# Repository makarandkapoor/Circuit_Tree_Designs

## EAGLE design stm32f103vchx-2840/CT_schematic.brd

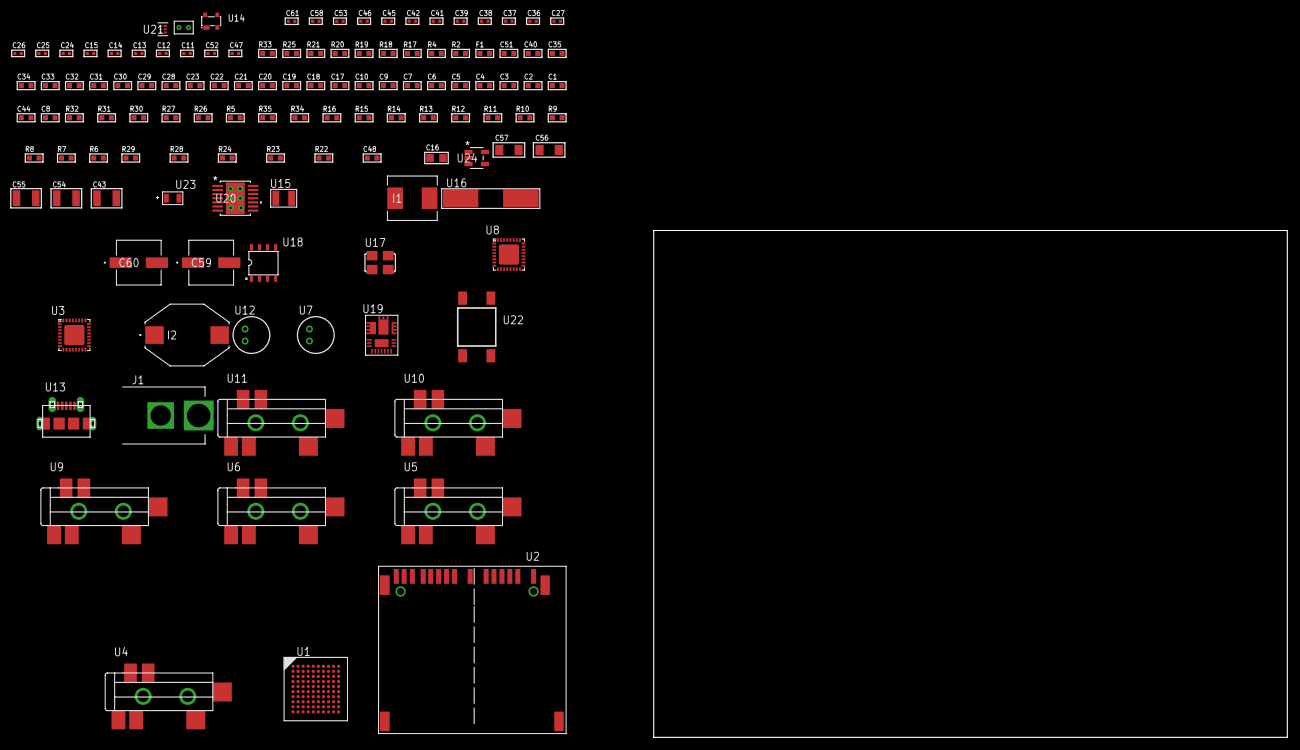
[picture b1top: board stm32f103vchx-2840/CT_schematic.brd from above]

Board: 2 copper layers, 121 parts (0 on the bottom side), 82 nets, no tracks yet.

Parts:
C1, C10, C17, C18, C19, C20, C21, C22, C23, C28, C29, C30, C31, C32, C33, C34, C35, C40, C51: 1e-06; C0603
C2, C3, C4, C5, C6, C7: 1e-07; C0603
C8: 4.7e-06; C0603
C9: 1e-08; C0603
C11, C12, C13, C14: 1e-11; C0402
C15, C24, C25, C26, C27, C36, C37, C38, C39, C45, C46, C53, C58: 1e-07; C0402
C16: 1e-05; C0805
C41, C42, C61: 1e-08; C0402
C43: 0.0001; C1210
C44: 2.2e-06; C0603
C47: 8.2e-09; C0402
C48: 2.724074888439e-07; R0603
C52: 3.3e-09; C0402
C54, C55: 2.2e-05; C1210
C56, C57: 1e-05; C1206
C59, C60: 0.0001; EXV-9H
F1: 240.0; L0603
I1: 6.8e-07; IND25X25CZ
I2: 1e-05; IND_PM3316
J1: PJ-037B; PJ-037B_PACKAGE
R2: 1000.0; R0603
R4: 4700.0; R0603
R5, R31, R32: 10000.0; R0603
R6, R7, R8, R9, R10, R11, R12, R13, R14, R15, R16: 100000.0; R0603
R17, R18, R19, R20: 1270.0; R0603
R21: 0.1; R0603
R22: 4030.2416170974; R0603
R23: 2878.7440122125; R0603
R24: 63.795609756098; R0603
R25: 130.0; R0603
R26: 39000.0; R0603
R27: 49900.0; R0603
R28: 5286.7027027027; R0603
R29: 71007.101651032; R0603
R30: 22000.0; R0603
R33: 9100.0; R0603
R34: 680000.0; R0603
R35: 120000.0; R0603
U1: stm32f103vch6; LFBGA100
U2: 10100565
U3, U8: SGTL5000XNAA3; QFN-32
U4, U5, U6, U9, U10, U11: SJ-43515TS-SMT-TR
U7, U12: WM-64PCT; WM-64PC
U13: 47590-0001; MICRO_USB_AB
U14: prtr5v0u2ax; SOT143B
U15: ABS07-32.768KHZ-7-T
U16: ABLS-25.000MHZ-B2F-T
U17: ASFL-24.57MHZ-NCS; ASFL1
U18: idt74fct38072; IDT74FCT38072
U19: IR3899MTR1PBF
U20: tps54225PWP; HTSSOP14
U21: TPS3895ADRYR; SON-6
U22: 4-1437565-2; SW_4-1437565-2
U23: Q65110A2395; LGM67K-G1J2-24-Z
U24: nc7sz125m5x; NC7SZ125M5X
U25: Dummy; DUMMY_PACKAGE_235

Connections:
CLK_CRYSTAL_U1_A1: C11.1, U1.A1, U15.1
CLK_CRYSTAL_U1_B1: C12.1, U1.B1, U15.2
CLK_CRYSTAL_U1_C1: C13.1, U1.C1, U16.1
CLK_CRYSTAL_U1_D1: C14.1, U1.D1, U16.2
CLK_U3_21: U3.21, U18.7
CLK_U8_21: U8.21, U18.6
CLK_U18_3: U17.3, U18.3
GND: C1.2, C2.2, C3.2, C4.2, C5.2, C6.2, C7.2, C8.2, C9.2, C10.2, C11.2, C12.2, C13.2, C14.2, C15.2, C16.2, C24.2, C25.2, C26.2, C27.2, C28.2, C36.2, C37.2, C38.2, C39.2, C40.2, C41.2, C42.2, C44.2, C45.2, C46.2, C51.2, C52.2, C54.2, C55.2, C56.2, C57.2, C58.2, C59.2, C60.2, C61.2, J1.2, R2.2, R5.2, R18.2, R20.2, R21.1, R21.2, R23.2, R26.2, R28.2, R30.2, R33.2, R35.2, U1.C2, U1.E4, U1.E5, U1.E6, U1.E7, U1.G1, U1.H1, U2.6, U2.10, U2.12, U2.16, U2.17, U2.20, U2.21, U3.1, U3.3, U3.7, U3.EXP, U5.1, U6.1, U7.2, U8.1, U8.3, U8.7, U8.EXP, U10.1, U11.1, U12.2, U13.5, U13.6, U13.7, U13.8, U13.9, U14.1, U17.2, U18.4, U18.5, U18.8, U19.4, U19.11, U19.17, U20.5, U20.8, U20.9, U20.15, U21.2, U23.C, U24.1, U24.3, U25.1
NET_U1_D5: R5.1, U1.D5
NET_U1_E1: R4.1, U1.E1, U24.4
NET_U1_K1: C9.1, C10.1, F1.1, U1.J1, U1.K1
NET_U1_K10: U22.3, U22.4
NET_U2_1: R8.1, U2.1
NET_U2_2: R7.1, U2.2
NET_U2_18: U2.18, U2.19
NET_U3_10: C27.1, U3.10
NET_U3_29: R17.1, U3.29
NET_U3_31: R18.1, U3.31
NET_U4_1: U3.4, U4.1
NET_U4_2: U3.2, U4.2
NET_U4_5: U3.6, U4.5
NET_U5_2: C18.1, U5.2
NET_U5_5: C17.1, U5.5
NET_U6_2: C20.1, C21.1, U6.2
NET_U6_5: C19.1, U6.5
NET_U6_13: C20.2, C21.2
NET_U7_1: C22.1, C23.1, C28.1, U3.16, U7.1
NET_U7_15: C22.2, C23.2
NET_U8_10: C39.1, U8.10
NET_U8_29: R19.1, U8.29
NET_U8_31: R20.1, U8.31
NET_U9_1: U8.4, U9.1
NET_U9_2: U8.2, U9.2
NET_U9_5: U8.6, U9.5
NET_U10_2: C30.1, U10.2
NET_U10_5: C29.1, U10.5
NET_U11_2: C32.1, C33.1, U11.2
NET_U11_5: C31.1, U11.5
NET_U11_13: C32.2, C33.2
NET_U12_1: C34.1, C35.1, C40.1, U8.16, U12.1
NET_U12_15: C34.2, C35.2
NET_U14_4: U13.1, U14.4
NET_U19_1: C47.1, R22.1, R23.1, R24.1, R25.1, U19.1, U19.8
NET_U19_2: C46.1, U19.2
NET_U19_3: C47.2, C48.1, C48.2, U19.3
NET_U19_5: R26.1, U19.5
NET_U19_10: C44.1, U19.10
NET_U19_12: C43.1, I1.1, U19.12
NET_U19_14: C43.2, U19.14
NET_U19_15: R27.1, R28.1, U19.15
NET_U19_ATNET_3: I1.2, R22.2
NET_U19_ATNET_4: C48.2, R24.2
NET_U20_2: R29.2, R30.1, U20.2
NET_U20_3: C51.1, U20.3
NET_U20_4: C52.1, U20.4
NET_U20_10: C53.1, I2.1, U20.10, U20.11
NET_U20_12: C53.2, U20.12
NET_U21_1: R32.1, R33.1, U21.1
NET_U21_3: R34.2, R35.1, U21.3
NET_U21_4: R31.1, U21.4, U24.2
NET_U22_1: R2.1, U22.1, U22.2
PROC_DAC_OUT2: U1.H3, U25.2
PROC_I2S2_CK: U1.J8, U3.24
PROC_I2S2_SD: U1.G8, U3.26
PROC_I2S2_WS: U1.K8, U3.23
PROC_I2S3_CK: U1.A7, U8.24
PROC_I2S3_SD: U1.C5, U8.26
PROC_I2S3_WS: U1.A8, U8.23
PROC_SDIO_CK: R6.1, U1.C8, U2.8
PROC_SDIO_D0: R9.1, U1.F9, U2.4
PROC_SDIO_D1: R10.1, U1.E9, U2.3
PROC_SDIO_D2: R11.1, U1.B9, U2.15
PROC_SDIO_D3: R12.1, U1.B8, U2.14
PROC_SDIO_D4: R13.1, U1.B4, U2.13
PROC_SDIO_D5: R14.1, U1.A4, U2.11
PROC_SDIO_D6: R15.1, U1.F10, U2.7
PROC_SDIO_D7: R16.1, U1.E10, U2.5
PROC_USB_DM: U13.2, U14.3
PROC_USB_DP: U13.3, U14.2
VCC_S1_16V4: C45.1, C56.1, C57.1, C59.1, C60.1, J1.1, R27.2, U19.9, U20.7, U20.13, U20.14
VCC_TIER1_1V2: C24.1, C36.1, I1.2, R22.2, U3.30, U8.30
VCC_TIER1_3V3: C1.1, C2.1, C3.1, C4.1, C5.1, C6.1, C7.1, C8.1, C15.1, C16.1, C25.1, C26.1, C37.1, C38.1, C41.1, C42.1, C54.1, C55.1, C58.1, C61.1, F1.2, I2.2, R4.2, R6.2, R7.2, R8.2, R9.2, R10.2, R11.2, R12.2, R13.2, R14.2, R15.2, R16.2, R17.2, R19.2, R29.1, R31.2, R32.2, R34.1, U1.B2, U1.D2, U1.F4, U1.F5, U1.F6, U1.F7, U2.9, U3.5, U3.20, U8.5, U8.20, U17.4, U18.1, U18.2, U20.1, U21.6, U24.5

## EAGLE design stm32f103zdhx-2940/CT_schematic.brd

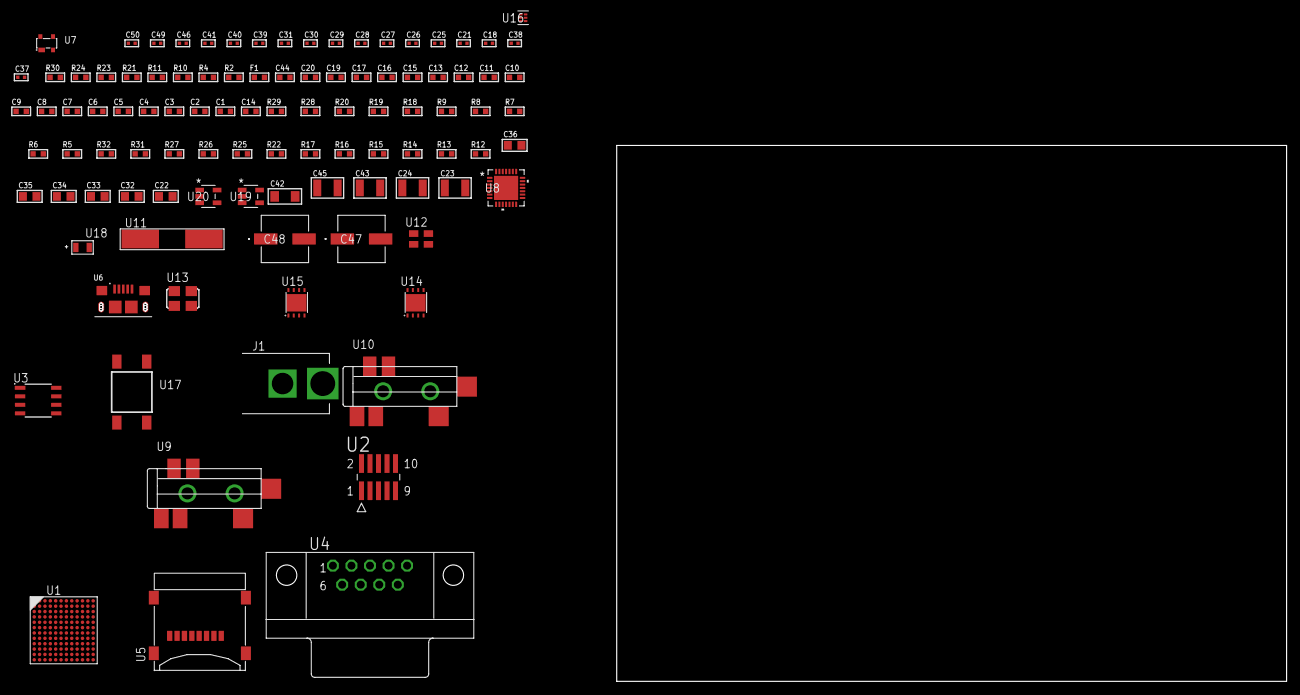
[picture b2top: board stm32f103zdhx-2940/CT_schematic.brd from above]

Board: 2 copper layers, 102 parts (0 on the bottom side), 48 nets, no tracks yet.

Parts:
C1, C17, C19, C20, C44: 1e-06; C0603
C2, C3, C4, C5, C6, C7, C8, C9, C10, C11, C12, C13: 1e-07; C0603
C14: 4.7e-06; C0603
C15, C16: 1e-08; C0603
C18, C21, C27, C28, C29, C30, C31, C46: 1e-07; C0402
C22, C32, C33, C34, C35, C36: 1e-05; C0805
C23, C24: 2.2e-05; C1210
C25, C26: 1e-09; C0402
C37, C38: 2.2e-11; C0402
C39, C40, C41, C49, C50: 1e-08; C0402
C42: 1e-05; C1206
C43, C45: 1e-05; C1210
C47, C48: 0.0001; EXV-9H
F1: 240.0; L0603
J1: PJ-037B; PJ-037B_PACKAGE
R2, R24: 1000.0; R0603
R4: 4700.0; R0603
R5, R6, R7, R8, R9, R28, R29: 10000.0; R0603
R10: 5.0; R0603
R11: 120.0; R0603
R12, R13, R14, R15, R16, R17, R22, R25, R27: 100000.0; R0603
R18, R19, R20: 47000.0; R0603
R21: 680.0; R0603
R23: 2231.0; R0603
R26: 300000.0; R0603
R30: 9100.0; R0603
R31: 680000.0; R0603
R32: 120000.0; R0603
U1: stm32f103zdh6; LFBGA144
U2: FTSH-105-01-L-DV-K; SAMTEC_FTSH-105-01-L-DV-K
U3: MCP2562-E/SN; SOIC-8
U4: 182-009-113R531; 182-009-MALE
U5: 0472192001; MOLEX_47219-2001
U6: 10118193-0001LF; FCI_10118193-0001LF
U7: prtr5v0u2ax; SOT143B
U8: WM8731CLSEFL; QFN-28
U9, U10: SJ-43515TS-SMT-TR
U11: ABLS-12.288MHZ-B4-T
U12: ASEK-32.768KHz-ECST; ASEK
U13: ASFL1-25MHZ-NCS; ASFL1
U14: LP3878SDX-ADJ/NOPB; WSON-8
U15: LP2951ACSDX/NOPB; WSON-8
U16: TPS3895ADRYR; SON-6
U17: 4-1437565-2; SW_4-1437565-2
U18: Q65110A2395; LGM67K-G1J2-24-Z
U19, U20: nc7sz125m5x; NC7SZ125M5X

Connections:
CLK_CRYSTAL_U8_1: C37.1, U8.1, U11.1
CLK_CRYSTAL_U8_2: C38.1, U8.2, U11.2
CLK_U1_B1: U1.B1, U12.3
CLK_U1_D1: U1.D1, U13.3
GND: C1.2, C2.2, C3.2, C4.2, C5.2, C6.2, C7.2, C8.2, C9.2, C10.2, C11.2, C12.2, C13.2, C14.2, C15.2, C16.2, C17.2, C18.2, C19.2, C20.2, C21.2, C22.2, C26.2, C27.2, C28.2, C29.2, C30.2, C31.2, C32.2, C33.2, C34.2, C35.2, C36.2, C37.2, C38.2, C39.2, C40.2, C41.2, C42.2, C43.2, C44.2, C45.2, C46.2, C47.2, C48.2, C49.2, C50.2, J1.2, R2.2, R5.2, R9.2, R10.2, R18.2, R19.2, R20.2, R24.2, R27.2, R30.2, R32.2, U1.D2, U1.E5, U1.E6, U1.E7, U1.G4, U1.G8, U1.G9, U1.G10, U1.H5, U1.H6, U1.H7, U1.J1, U1.K1, U2.3, U2.5, U3.2, U3.8, U4.5, U5.6, U5.G1, U5.G2, U5.G3, U5.G4, U6.5, U6.6, U6.7, U6.8, U6.9, U7.1, U8.4, U8.15, U8.19, U8.25, U8.26, U8.29, U9.1, U10.1, U12.2, U13.2, U14.3, U14.PAD, U15.3, U15.4, U15.PAD, U16.2, U18.C, U19.2, U19.3, U20.1, U20.3
NET_U1_D5: R5.1, U1.D5
NET_U1_F1: R4.1, U1.F1, U20.4
NET_U1_M1: C15.1, C16.1, C17.1, F1.1, U1.L1, U1.M1
NET_U1_M10: U17.3, U17.4
NET_U2_2: R8.1, U2.2
NET_U2_9: R10.1, U2.9
NET_U3_6: R11.2, U3.6
NET_U4_2: R11.2, U3.6, U4.2
NET_U4_3: R11.1, U3.7, U4.3
NET_U7_4: U6.1, U7.4
NET_U8_20: C31.1, C36.1, U8.20
NET_U9_2: C24.1, R19.1, U9.2
NET_U9_5: C23.1, R18.1, U9.5
NET_U10_5: C25.1, C26.1, R20.1, R21.1, U10.5
NET_U14_1: C41.1, U14.1
NET_U14_6: R23.2, R24.1, U14.6
NET_U14_8: R22.1, U14.8
NET_U15_5: R25.1, U15.5
NET_U15_7: R26.2, R27.1, U15.7
NET_U16_1: R29.1, R30.1, U16.1
NET_U16_3: R31.2, R32.1, U16.3
NET_U16_4: R28.1, U16.4, U19.4, U20.2
NET_U17_1: R2.1, U17.1, U17.2
PROC_CAN_RX: U1.C5, U3.4
PROC_CAN_TX: U1.B5, U3.1
PROC_I2S2_CK: U1.M12, U8.7
PROC_I2S2_SD: U1.L12, U8.8
PROC_I2S2_WS: U1.M11, U8.9, U8.11
PROC_SDIO_CK: R13.1, U1.C10, U5.5
PROC_SDIO_CMD: R12.1, U1.E9, U5.3
PROC_SDIO_D0: R14.1, U1.F11, U5.7
PROC_SDIO_D1: R15.1, U1.E11, U5.8
PROC_SDIO_D2: R16.1, U1.B11, U5.1
PROC_SDIO_D3: R17.1, U1.B10, U5.2
PROC_SYS_JTDI: R7.1, U1.A10, U2.8
PROC_SYS_JTDO_TRACESWO: U1.A7, U2.6
PROC_SYS_TRACECLK: R9.1, U1.A3, U2.4
PROC_USB_DM: U6.2, U7.3
PROC_USB_DP: U6.3, U7.2
RST_OUT_U2_JTAG_RST_B: R6.1, U2.10, U19.1
VCC_S1_8V1: C42.1, C44.1, C47.1, C48.1, J1.1, R22.2, U14.4, U15.8
VCC_TIER1_3V3: C1.1, C2.1, C3.1, C4.1, C5.1, C6.1, C7.1, C8.1, C9.1, C10.1, C11.1, C12.1, C13.1, C14.1, C18.1, C20.1, C21.1, C22.1, C27.1, C28.1, C29.1, C30.1, C32.1, C33.1, C34.1, C35.1, C39.1, C40.1, C43.1, C46.1, C49.1, C50.1, F1.2, R4.2, R6.2, R7.2, R8.2, R12.2, R13.2, R14.2, R15.2, R16.2, R17.2, R23.1, R28.2, R29.2, R31.1, U1.C2, U1.D3, U1.F4, U1.F5, U1.F6, U1.F7, U1.F8, U1.F9, U1.F10, U1.G5, U1.G6, U1.G7, U2.1, U3.5, U5.4, U8.3, U8.5, U8.12, U8.18, U12.4, U13.4, U14.5, U16.6, U19.5, U20.5
VCC_TIER1_5V0: C19.1, C45.1, R25.2, R26.1, U3.3, U15.1

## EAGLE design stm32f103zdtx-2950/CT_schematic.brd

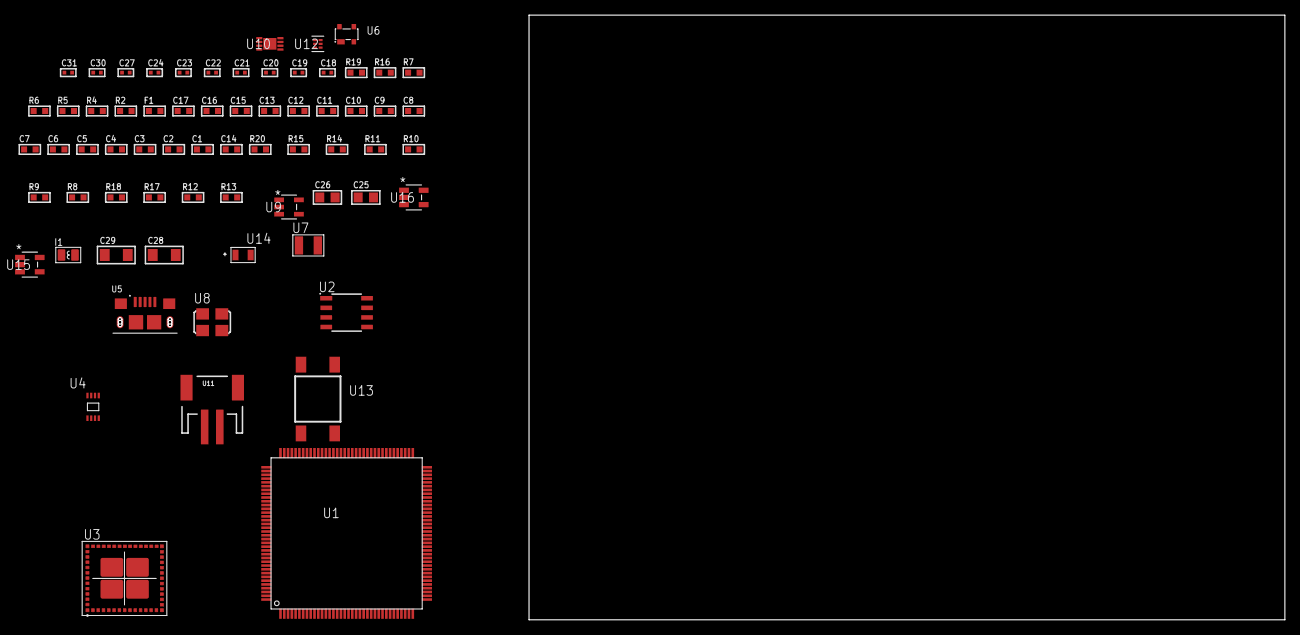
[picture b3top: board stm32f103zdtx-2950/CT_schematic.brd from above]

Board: 2 copper layers, 154.3 x 80.0 mm, 67 parts (0 on the bottom side), 33 nets, no tracks yet.

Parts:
C1, C17: 1e-06; C0603
C2, C3, C4, C5, C6, C7, C8, C9, C10, C11, C12, C13: 1e-07; C0603
C14: 4.7e-06; C0603
C15, C16: 1e-08; C0603
C18, C19: 1e-11; C0402
C20, C23, C24, C30, C31: 1e-08; C0402
C21, C22, C27: 1e-07; C0402
C25, C26: 1e-05; C0805
C28, C29: 1e-05; C1206
F1: 240.0; L0603
I1: 1.5e-06; L0806
R2: 1000.0; R0603
R4, R5: 4700.0; R0603
R6, R7: 2200.0; R0603
R8, R9, R10, R11, R14, R15, R20: 10000.0; R0603
R12: 220000.0; R0603
R13: 1000000.0; R0603
R16: 9100.0; R0603
R17: 680000.0; R0603
R18: 120000.0; R0603
R19: 2000.0; R0603
U1: stm32f103zdt7; LQFP144
U2: AT25640B-SSHL-T; SOIC-8
U3: MBH7BLZ02-109004
U4: 24AA08T-I/MNY; TDFN-8/6MM
U5: 10118193-0001LF; FCI_10118193-0001LF
U6: prtr5v0u2ax; SOT143B
U7: ABS07-32.768KHZ-7-T
U8: ASFL1-25MHZ-NCS; ASFL1
U9: ltc3406es5; TSOT-23-5
U10: MCP73831T-2ACI/MC; DFN8_2X3MC
U11: S2B-PH-SM4-TB(LF)(SN); JST-2-SMD
U12: TPS3895ADRYR; SON-6
U13: 4-1437565-2; SW_4-1437565-2
U14: Q65110A2395; LGM67K-G1J2-24-Z
U15, U16: nc7sz125m5x; NC7SZ125M5X

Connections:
CLK_CRYSTAL_U1_8: C18.1, U1.8, U7.1
CLK_CRYSTAL_U1_9: C19.1, U1.9, U7.2
CLK_U1_23: U1.23, U8.3
GND: C1.2, C2.2, C3.2, C4.2, C5.2, C6.2, C7.2, C8.2, C9.2, C10.2, C11.2, C12.2, C13.2, C14.2, C15.2, C16.2, C17.2, C18.2, C19.2, C20.2, C21.2, C22.2, C23.2, C24.2, C25.2, C26.1, C26.2, C27.2, C28.2, C29.2, C30.2, C31.2, R2.2, R8.2, R12.2, R16.2, R18.2, R19.2, U1.16, U1.30, U1.31, U1.38, U1.51, U1.61, U1.71, U1.83, U1.94, U1.107, U1.120, U1.130, U1.143, U2.4, U3.1, U3.3, U3.15, U3.27, U3.29, U3.41, U3.42, U3.43, U3.44, U3.45, U3.46, U3.47, U3.48, U3.49, U3.50, U3.52, U3.53, U3.54, U3.55, U3.56, U4.4, U5.5, U5.6, U5.7, U5.8, U5.9, U6.1, U8.2, U9.2, U10.6, U10.9, U11.2, U12.2, U14.C, U15.1, U15.3, U16.1, U16.3
INPUT_USBPOWER_5V: C28.1, R20.2, U5.1, U6.4, U10.1, U10.2
NET_U1_25: R5.1, U1.25, U16.4
NET_U1_33: C15.1, C16.1, C17.1, F1.1, U1.32, U1.33
NET_U1_136: R6.1, U1.136, U4.6
NET_U1_137: R7.1, U1.137, U4.5
NET_U1_138: R8.1, U1.138
NET_U1_142: U13.3, U13.4
NET_U2_3: R9.1, U2.3
NET_U2_7: R11.1, U2.7
NET_U3_39: R4.1, U3.39, U15.4
NET_U9_3: I1.1, U9.3
NET_U9_5: R12.1, R13.1, U9.5
NET_U9_ATNET_3: I1.2, R13.2
NET_U10_5: R20.1, U10.5
NET_U10_8: R19.1, U10.8
NET_U12_1: R15.1, R16.1, U12.1
NET_U12_3: R17.2, R18.1, U12.3
NET_U12_4: R14.1, U12.4, U15.2, U16.2
NET_U13_1: R2.1, U13.1, U13.2
PROC_SPI1_MISO: U1.42, U2.2
PROC_SPI1_MOSI: U1.43, U2.5
PROC_SPI1_NSS: R10.1, U1.40, U2.1
PROC_SPI1_SCK: U1.41, U2.6
PROC_UART4_RX: U1.112, U3.25
PROC_UART4_TX: U1.111, U3.23
PROC_USB_DM: U1.103, U5.2, U6.3
PROC_USB_DP: U1.104, U5.3, U6.2
VCC_S1_3V7: C25.1, C29.1, U9.4, U10.3, U10.4, U11.1
VCC_TIER1_3V3: C1.1, C2.1, C3.1, C4.1, C5.1, C6.1, C7.1, C8.1, C9.1, C10.1, C11.1, C12.1, C13.1, C14.1, C20.1, C21.1, C22.1, C23.1, C24.1, C26.2, C27.1, C30.1, C31.1, F1.2, I1.2, R4.2, R5.2, R6.2, R7.2, R9.2, R10.2, R11.2, R13.2, R14.2, R15.2, R17.1, U1.6, U1.17, U1.39, U1.52, U1.62, U1.72, U1.84, U1.95, U1.108, U1.121, U1.131, U1.144, U2.8, U3.28, U4.7, U4.8, U8.4, U12.6, U15.5, U16.5

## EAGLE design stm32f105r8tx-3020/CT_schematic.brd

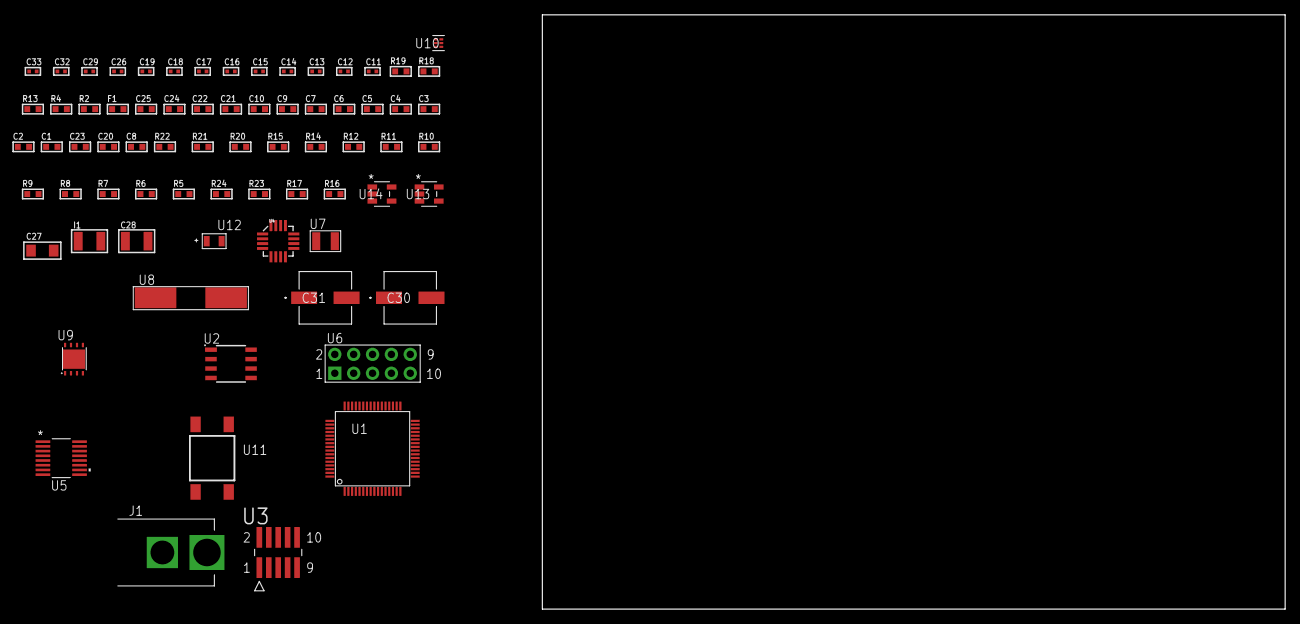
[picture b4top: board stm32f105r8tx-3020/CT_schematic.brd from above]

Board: 2 copper layers, 100.0 x 80.0 mm, 72 parts (0 on the bottom side), 46 nets, no tracks yet.

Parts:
C1, C10, C21, C22, C24, C25: 1e-06; C0603
C2, C3, C4, C5, C6, C7: 1e-07; C0603
C8: 4.7e-06; C0603
C9: 1e-08; C0603
C11, C12, C13, C14: 1e-11; C0402
C15, C17, C18, C19, C26, C32, C33: 1e-08; C0402
C16, C29: 1e-07; C0402
C20: 4.7e-07; C0603
C23: 2.2e-07; C0603
C27: 1e-05; C1206
C28: 1e-05; C1210
C30, C31: 0.0001; EXV-9H
F1: 240.0; L0603
I1: 1e-05; L1210
J1: PJ-037B; PJ-037B_PACKAGE
R2, R19: 1000.0; R0603
R4: 4700.0; R0603
R5, R6, R7, R8, R9, R10, R11, R12, R14, R15, R20, R21: 10000.0; R0603
R13: 5.0; R0603
R16, R17: 100000.0; R0603
R18: 1500.0; R0603
R22: 18000.0; R0603
R23: 470000.0; R0603
R24: 120000.0; R0603
U1: stm32f105r8t7; LQFP64
U2: AT25512N-SH-T; SOIC-8
U3: FTSH-105-01-L-DV-K; SAMTEC_FTSH-105-01-L-DV-K
U4: l3g4200d; LGA-16
U5: LTC2804CGN-1#PBF; SSOP-16
U6: HTSS-105-01-G-D
U7: ABS07-32.768KHZ-7-T
U8: ABLS-25.000MHZ-B2F-T
U9: LP3878SDX-ADJ/NOPB; WSON-8
U10: TPS3895ADRYR; SON-6
U11: 4-1437565-2; SW_4-1437565-2
U12: Q65110A2395; LGM67K-G1J2-24-Z
U13, U14: nc7sz125m5x; NC7SZ125M5X

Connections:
CLK_CRYSTAL_U1_3: C11.1, U1.3, U7.1
CLK_CRYSTAL_U1_4: C12.1, U1.4, U7.2
CLK_CRYSTAL_U1_5: C13.1, U1.5, U8.1
CLK_CRYSTAL_U1_6: C14.1, U1.6, U8.2
GND: C1.2, C2.2, C3.2, C4.2, C5.2, C6.2, C7.2, C8.2, C9.2, C10.2, C11.2, C12.2, C13.2, C14.2, C15.2, C16.2, C17.2, C18.2, C19.2, C21.2, C22.2, C24.2, C25.2, C26.2, C27.2, C28.2, C29.2, C30.2, C31.2, C32.2, C33.2, J1.2, R2.2, R5.2, R12.2, R13.2, R14.1, R14.2, R19.2, R22.2, R24.2, U1.12, U1.18, U1.31, U1.47, U1.63, U2.4, U3.3, U3.5, U4.8, U4.9, U4.10, U4.11, U4.12, U4.13, U5.8, U6.9, U9.3, U9.PAD, U10.2, U12.C, U13.2, U13.3, U14.1, U14.3
NET_U1_7: R4.1, U1.7, U14.4
NET_U1_13: C9.1, C10.1, F1.1, U1.13
NET_U1_60: R5.1, U1.60
NET_U1_62: U11.3, U11.4
NET_U2_3: R6.1, U2.3
NET_U2_7: R8.1, U2.7
NET_U3_2: R11.1, U3.2
NET_U3_4: R12.1, U3.4
NET_U3_9: R13.1, U3.9
NET_U4_14: C19.1, C20.1, U4.14
NET_U5_6: C21.1, U5.6
NET_U5_7: C23.1, I1.2, U5.7
NET_U5_9: C22.1, U5.9
NET_U5_10: C23.2, U5.10
NET_U5_11: R16.1, U5.11
NET_U6_3: U5.1, U6.3
NET_U6_4: U5.2, U6.4
NET_U6_5: U5.3, U6.5
NET_U6_6: U5.4, U6.6
NET_U9_1: C26.1, U9.1
NET_U9_6: R18.2, R19.1, U9.6
NET_U9_8: R17.1, U9.8
NET_U10_1: R21.1, R22.1, U10.1
NET_U10_3: R23.2, R24.1, U10.3
NET_U10_4: R20.1, U10.4, U13.4, U14.2
NET_U11_1: R2.1, U11.1, U11.2
PROC_SPI1_MISO: U1.22, U4.4
PROC_SPI1_MOSI: U1.23, U4.3
PROC_SPI1_NSS: R15.1, U1.20, U4.5
PROC_SPI1_SCK: U1.21, U4.2
PROC_SPI2_MISO: U1.35, U2.2
PROC_SPI2_MOSI: U1.36, U2.5
PROC_SPI2_NSS: R7.1, U1.33, U2.1
PROC_SPI2_SCK: U1.34, U2.6
PROC_SYS_JTDI: R10.1, U1.50, U3.8
PROC_SYS_JTDO: U1.55, U3.6
PROC_UART4_RX: U1.52, U5.16
PROC_UART4_TX: U1.51, U5.14
RST_OUT_U3_JTAG_RST_B: R9.1, U3.10, U13.1
VCC_S1_5V8: C27.1, C30.1, C31.1, J1.1, R17.2, U9.4
VCC_TIER1_2V5: C1.1, C2.1, C3.1, C4.1, C5.1, C6.1, C7.1, C8.1, C15.1, C16.1, C17.1, C18.1, C24.1, C25.1, C28.1, C29.1, C32.1, C33.1, F1.2, I1.1, R4.2, R6.2, R7.2, R8.2, R9.2, R10.2, R11.2, R15.2, R16.2, R18.1, R20.2, R21.2, R23.1, U1.1, U1.19, U1.32, U1.48, U1.64, U2.8, U3.1, U4.1, U4.15, U4.16, U5.5, U5.12, U9.5, U10.6, U13.5, U14.5

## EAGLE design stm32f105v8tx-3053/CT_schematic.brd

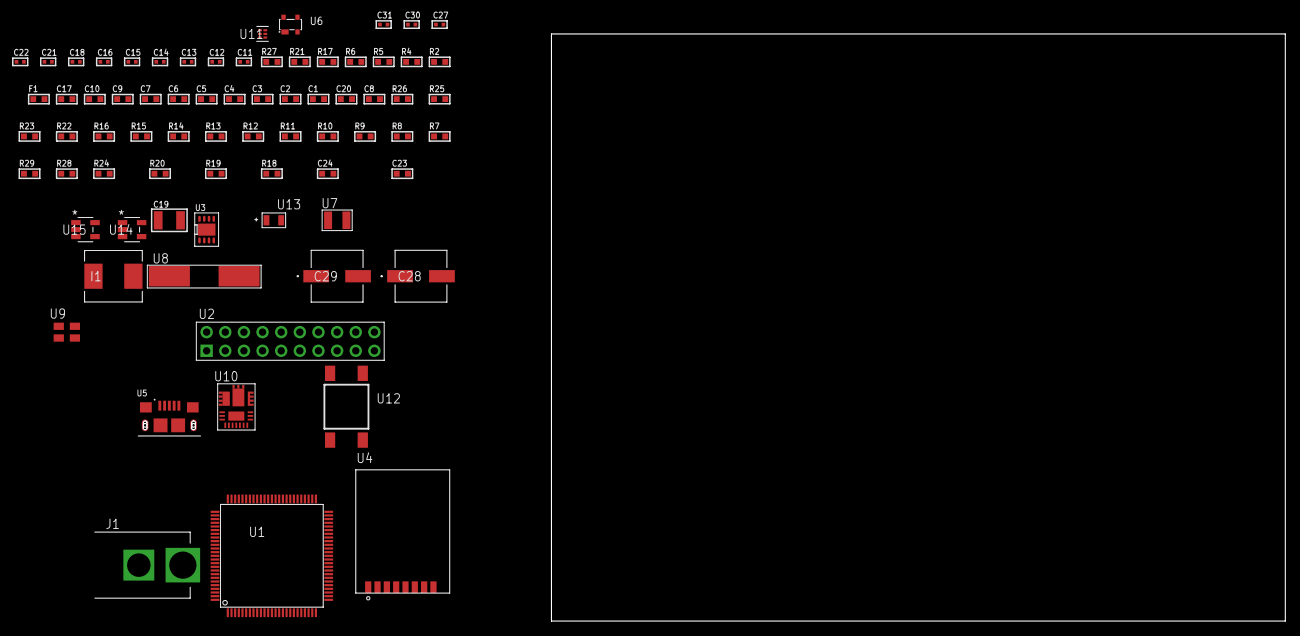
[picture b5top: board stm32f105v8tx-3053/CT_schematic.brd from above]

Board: 2 copper layers, 74 parts (0 on the bottom side), 44 nets, no tracks yet.

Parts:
C1, C10, C17: 1e-06; C0603
C2, C3, C4, C5, C6, C7: 1e-07; C0603
C8: 4.7e-06; C0603
C9: 1e-08; C0603
C11, C12: 1e-11; C0402
C13, C14, C15, C16, C21, C22, C27: 1e-07; C0402
C18, C30, C31: 1e-08; C0402
C19: 0.0001; C1210
C20: 2.2e-06; C0603
C23: 8.6971073877236e-09; R0603
C24: 2.9649229730876e-07; R0603
C28, C29: 0.0001; EXV-9H
F1: 240.0; L0603
I1: 6.8e-07; IND25X25CZ
J1: PJ-037B; PJ-037B_PACKAGE
R2: 1000.0; R0603
R4: 4700.0; R0603
R5, R6: 2200.0; R0603
R7, R8, R9, R10, R11, R12, R13, R14, R15, R16, R25, R26: 10000.0; R0603
R17: 0.1; R0603
R18: 4030.2416170974; R0603
R19: 719.68600305311; R0603
R20: 58.613333333333; R0603
R21: 130.0; R0603
R22: 39000.0; R0603
R23: 49900.0; R0603
R24: 5147.5789473684; R0603
R27: 9100.0; R0603
R28: 680000.0; R0603
R29: 120000.0; R0603
U1: stm32f105v8t6; LQFP100
U2: TST-110-05-T-D-RA
U3: PCF85063TP/1Z; SON-8
U4: RFM75-S
U5: 10118193-0001LF; FCI_10118193-0001LF
U6: prtr5v0u2ax; SOT143B
U7: ABS07-32.768KHZ-7-T
U8: ABLS-25.000MHZ-B2F-T
U9: ASEK-32.768KHz-ECST; ASEK
U10: IR3899MTR1PBF
U11: TPS3895ADRYR; SON-6
U12: 4-1437565-2; SW_4-1437565-2
U13: Q65110A2395; LGM67K-G1J2-24-Z
U14, U15: nc7sz125m5x; NC7SZ125M5X

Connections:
CLK_CRYSTAL_U1_12: C11.1, U1.12, U8.1
CLK_CRYSTAL_U1_13: C12.1, U1.13, U8.2
CLK_CRYSTAL_U3_1: U3.1, U7.1
CLK_CRYSTAL_U3_2: U3.2, U7.2
CLK_U1_8: U1.8, U9.3
GND: C1.2, C2.2, C3.2, C4.2, C5.2, C6.2, C7.2, C8.2, C9.2, C10.2, C11.2, C12.2, C13.2, C14.2, C15.2, C16.2, C17.2, C18.2, C20.2, C21.2, C22.2, C27.2, C28.2, C29.2, C30.2, C31.2, J1.2, R2.2, R7.2, R13.2, R17.1, R17.2, R19.2, R22.2, R24.2, R27.2, R29.2, U1.10, U1.19, U1.20, U1.27, U1.49, U1.74, U1.99, U2.4, U2.6, U2.8, U2.10, U2.12, U2.14, U2.16, U2.18, U2.20, U3.4, U3.PAD, U4.1, U5.5, U5.6, U5.7, U5.8, U5.9, U6.1, U9.2, U10.4, U10.11, U10.17, U11.2, U13.C, U14.2, U14.3, U15.1, U15.3
NET_U1_14: R4.1, U1.14, U15.4
NET_U1_22: C9.1, C10.1, F1.1, U1.21, U1.22
NET_U1_92: R5.1, U1.92, U3.6
NET_U1_93: R6.1, U1.93, U3.5
NET_U1_94: R7.1, U1.94
NET_U1_98: U12.3, U12.4
NET_U2_3: R8.1, U2.3
NET_U2_7: R10.1, U2.7
NET_U2_9: R11.1, U2.9
NET_U2_19: R13.1, U2.19
NET_U3_3: R14.1, U3.3
NET_U4_3: R15.1, U4.3
NET_U10_1: C23.1, R18.1, R19.1, R20.1, R21.1, U10.1, U10.8
NET_U10_2: C22.1, U10.2
NET_U10_3: C23.2, C24.1, C24.2, U10.3
NET_U10_5: R22.1, U10.5
NET_U10_10: C20.1, U10.10
NET_U10_12: C19.1, I1.1, U10.12
NET_U10_14: C19.2, U10.14
NET_U10_15: R23.1, R24.1, U10.15
NET_U10_ATNET_3: I1.2, R18.2
NET_U10_ATNET_4: C24.2, R20.2
NET_U11_1: R26.1, R27.1, U11.1
NET_U11_3: R28.2, R29.1, U11.3
NET_U11_4: R25.1, U11.4, U14.4, U15.2
NET_U12_1: R2.1, U12.1, U12.2
PROC_SPI1_MISO: U1.31, U4.7
PROC_SPI1_MOSI: U1.32, U4.6
PROC_SPI1_NSS: R16.1, U1.29, U4.4
PROC_SPI1_SCK: U1.30, U4.5
PROC_SYS_JTDI: R9.1, U1.77, U2.5
PROC_SYS_JTDO: U1.89, U2.13
PROC_USB_OTG_FS_DM: U1.70, U5.2, U6.3
PROC_USB_OTG_FS_DP: U1.71, U5.3, U6.2
PROC_USB_OTG_FS_VBUS: U1.68, U5.1, U6.4
RST_OUT_U2_SRESET_B: R12.1, U2.15, U14.1
VCC_S1_16V8: C21.1, C28.1, C29.1, J1.1, R23.2, U10.9
VCC_TIER1_3V3: C1.1, C2.1, C3.1, C4.1, C5.1, C6.1, C7.1, C8.1, C13.1, C14.1, C15.1, C16.1, C17.1, C18.1, C27.1, C30.1, C31.1, F1.2, I1.2, R4.2, R5.2, R6.2, R8.2, R9.2, R10.2, R11.2, R12.2, R14.2, R15.2, R16.2, R18.2, R25.2, R26.2, R28.1, U1.6, U1.11, U1.28, U1.50, U1.75, U1.100, U2.1, U2.2, U3.8, U4.2, U9.4, U11.6, U14.5, U15.5

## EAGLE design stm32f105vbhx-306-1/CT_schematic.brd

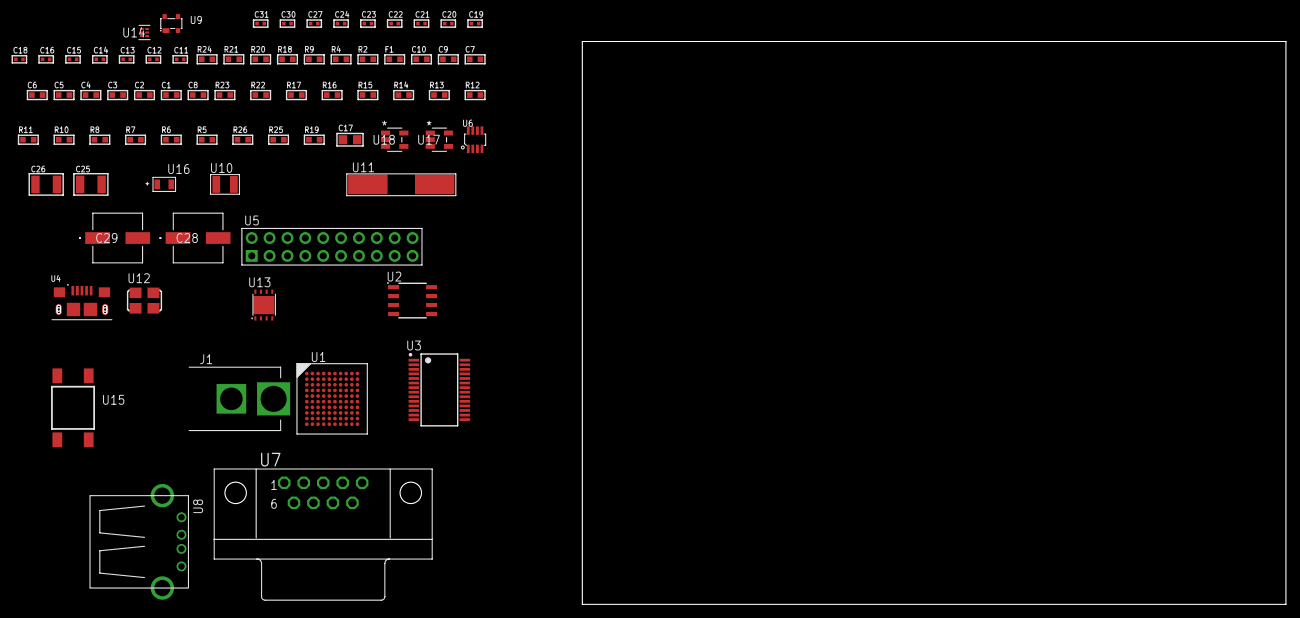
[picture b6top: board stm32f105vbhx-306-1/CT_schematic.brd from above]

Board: 2 copper layers, 75 parts (0 on the bottom side), 48 nets, no tracks yet.

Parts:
C1, C10: 1e-06; C0603
C2, C3, C4, C5, C6, C7: 1e-07; C0603
C8: 4.7e-06; C0603
C9: 1e-08; C0603
C11, C12, C13, C14: 1e-11; C0402
C15, C23, C24, C30, C31: 1e-08; C0402
C16, C18, C19, C20, C21, C22, C27: 1e-07; C0402
C17: 4.7e-06; C0805
C25, C26: 1e-05; C1210
C28, C29: 0.0001; EXV-9H
F1: 240.0; L0603
J1: PJ-037B; PJ-037B_PACKAGE
R2, R21: 1000.0; R0603
R4, R9: 4700.0; R0603
R5, R6, R7, R8, R10, R11, R12, R13, R14, R15, R16, R17, R22, R23: 10000.0; R0603
R18: 120.0; R0603
R19: 100000.0; R0603
R20: 2231.0; R0603
R24: 9100.0; R0603
R25: 680000.0; R0603
R26: 120000.0; R0603
U1: stm32f105vbh6; LFBGA100
U2: AT25080B-SSHL-T; SOIC-8
U3: FT232RL-REEL; SSOP-28
U4: 10118193-0001LF; FCI_10118193-0001LF
U5: TST-110-05-T-D-RA
U6: MAX3051EKA+T; SOT-23-8
U7: 182-009-113R531; 182-009-MALE
U8: 61400416021; USB-A-H
U9: prtr5v0u2ax; SOT143B
U10: ABS07-32.768KHZ-7-T
U11: ABLS-25.000MHZ-B2F-T
U12: ASFL1-12MHZ-NCS; ASFL1
U13: LP3878SDX-ADJ/NOPB; WSON-8
U14: TPS3895ADRYR; SON-6
U15: 4-1437565-2; SW_4-1437565-2
U16: Q65110A2395; LGM67K-G1J2-24-Z
U17, U18: nc7sz125m5x; NC7SZ125M5X

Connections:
CLK_CRYSTAL_U1_A1: C11.1, U1.A1, U10.1
CLK_CRYSTAL_U1_B1: C12.1, U1.B1, U10.2
CLK_CRYSTAL_U1_C1: C13.1, U1.C1, U11.1
CLK_CRYSTAL_U1_D1: C14.1, U1.D1, U11.2
CLK_U3_27: U3.27, U12.3
GND: C1.2, C2.2, C3.2, C4.2, C5.2, C6.2, C7.2, C8.2, C9.2, C10.2, C11.2, C12.2, C13.2, C14.2, C15.2, C16.2, C17.2, C18.2, C19.2, C20.2, C21.2, C22.2, C23.2, C24.2, C25.2, C26.2, C27.2, C28.2, C29.2, C30.2, C31.2, J1.2, R2.2, R5.2, R11.2, R17.2, R21.2, R24.2, R26.2, U1.C2, U1.E4, U1.E5, U1.E6, U1.E7, U1.G1, U1.H1, U2.4, U3.7, U3.18, U3.21, U3.25, U3.26, U4.5, U4.6, U4.7, U4.8, U4.9, U5.4, U5.6, U5.8, U5.10, U5.12, U5.14, U5.16, U5.18, U5.20, U6.2, U6.8, U7.5, U8.4, U8.5, U8.6, U9.1, U12.2, U13.3, U13.PAD, U14.2, U16.C, U17.2, U17.3, U18.1, U18.3
NET_U1_D5: R5.1, U1.D5
NET_U1_E1: R4.1, U1.E1, U18.4
NET_U1_K1: C9.1, C10.1, F1.1, U1.J1, U1.K1
NET_U1_K10: U15.3, U15.4
NET_U2_3: R6.1, U2.3
NET_U2_7: R8.1, U2.7
NET_U3_14: R10.1, U3.14
NET_U3_17: C18.1, U3.17
NET_U3_19: R11.1, U3.19
NET_U4_1: R9.1, U4.1
NET_U4_2: U3.16, U4.2
NET_U4_3: U3.15, U4.3
NET_U5_3: R12.1, U5.3
NET_U5_7: R14.1, U5.7
NET_U5_9: R15.1, U5.9
NET_U5_19: R17.1, U5.19
NET_U6_6: R18.2, U6.6
NET_U7_2: R18.2, U6.6, U7.2
NET_U7_3: R18.1, U6.7, U7.3
NET_U13_1: C24.1, U13.1
NET_U13_6: R20.2, R21.1, U13.6
NET_U13_8: R19.1, U13.8
NET_U14_1: R23.1, R24.1, U14.1
NET_U14_3: R25.2, R26.1, U14.3
NET_U14_4: R22.1, U14.4, U17.4, U18.2
NET_U15_1: R2.1, U15.1, U15.2
PROC_CAN1_RX: U1.B4, U6.4
PROC_CAN1_TX: U1.A4, U6.1
PROC_SPI1_MISO: U1.A6, U2.2
PROC_SPI1_MOSI: U1.C5, U2.5
PROC_SPI1_NSS: R7.1, U1.G3, U2.1
PROC_SPI1_SCK: U1.H3, U2.6
PROC_SYS_JTDI: R13.1, U1.A8, U5.5
PROC_SYS_JTDO: U1.A7, U5.13
PROC_UART4_RX: U1.B8, U3.1
PROC_UART4_TX: U1.B9, U3.5
PROC_USB_OTG_FS_DM: U1.C10, U8.2, U9.3
PROC_USB_OTG_FS_DP: U1.B10, U8.3, U9.2
PROC_USB_OTG_FS_VBUS: U1.C9, U8.1, U9.4
RST_OUT_U5_SRESET_B: R16.1, U5.15, U17.1
VCC_S1_15V2: C25.1, C28.1, C29.1, J1.1, R19.2, U13.4
VCC_TIER1_3V3: C1.1, C2.1, C3.1, C4.1, C5.1, C6.1, C7.1, C8.1, C15.1, C16.1, C17.1, C19.1, C20.1, C21.1, C22.1, C23.1, C26.1, C27.1, C30.1, C31.1, F1.2, R4.2, R6.2, R7.2, R8.2, R10.2, R12.2, R13.2, R14.2, R15.2, R16.2, R20.1, R22.2, R23.2, R25.1, U1.B2, U1.D2, U1.F4, U1.F5, U1.F6, U1.F7, U2.8, U3.4, U3.20, U5.1, U5.2, U6.3, U12.4, U13.5, U14.6, U17.5, U18.5

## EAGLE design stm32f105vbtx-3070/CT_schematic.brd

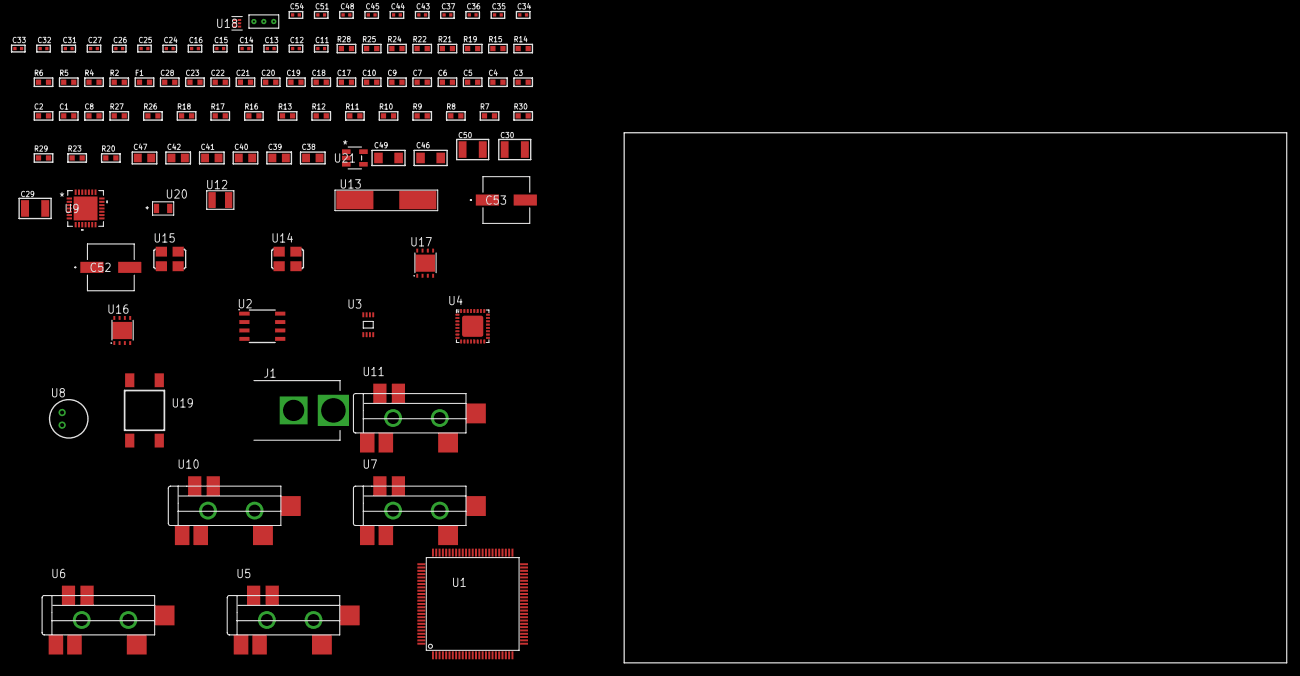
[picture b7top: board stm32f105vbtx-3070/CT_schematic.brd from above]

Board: 2 copper layers, 100.0 x 80.0 mm, 106 parts (0 on the bottom side), 60 nets, no tracks yet.

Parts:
C1, C10, C17, C18, C19, C20, C21, C22, C23, C28: 1e-06; C0603
C2, C3, C4, C5, C6, C7: 1e-07; C0603
C8: 4.7e-06; C0603
C9: 1e-08; C0603
C11, C12, C13, C14: 1e-11; C0402
C15, C16, C43, C44, C45, C48, C54: 1e-08; C0402
C24, C25, C26, C27, C33, C34, C35, C36, C37, C51: 1e-07; C0402
C29, C30: 2.2e-05; C1210
C31, C32: 1e-09; C0402
C38, C39, C40, C41, C42, C47: 1e-05; C0805
C46, C49: 1e-05; C1206
C50: 1e-05; C1210
C52, C53: 0.0001; EXV-9H
F1: 240.0; L0603
J1: PJ-037B; PJ-037B_PACKAGE
R2, R22, R25: 1000.0; R0603
R4: 4700.0; R0603
R5, R6: 2200.0; R0603
R7, R8, R9, R10, R11, R12, R13, R26, R27: 10000.0; R0603
R14, R15: 1270.0; R0603
R16, R17, R18: 47000.0; R0603
R19: 680.0; R0603
R20, R23: 100000.0; R0603
R21: 200.0; R0603
R24: 2231.0; R0603
R28: 9100.0; R0603
R29: 680000.0; R0603
R30: 120000.0; R0603
U1: stm32f105vbt7; LQFP100
U2: AT25040B-SSHL-T; SOIC-8
U3: 24AA128T-I/MNY; TDFN-8/6MM
U4: SGTL5000XNAA3; QFN-32
U5, U6, U7, U10, U11: SJ-43515TS-SMT-TR
U8: WM-64PCT; WM-64PC
U9: WM8731CLSEFL; QFN-28
U12: ABS07-32.768KHZ-7-T
U13: ABLS-25.000MHZ-B2F-T
U14: ASFL1-12.288MHZ-EC-T; ASFL1
U15: ASFL-24.57MHZ-NCS; ASFL1
U16, U17: LP3878SDX-ADJ/NOPB; WSON-8
U18: TPS3895ADRYR; SON-6
U19: 4-1437565-2; SW_4-1437565-2
U20: Q65110A2395; LGM67K-G1J2-24-Z
U21: nc7sz125m5x; NC7SZ125M5X
U22: Dummy; DUMMY_PACKAGE_220

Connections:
CLK_CRYSTAL_U1_8: C11.1, U1.8, U12.1
CLK_CRYSTAL_U1_9: C12.1, U1.9, U12.2
CLK_CRYSTAL_U1_12: C13.1, U1.12, U13.1
CLK_CRYSTAL_U1_13: C14.1, U1.13, U13.2
CLK_U4_21: U4.21, U15.3
CLK_U9_1: U9.1, U14.3
GND: C1.2, C2.2, C3.2, C4.2, C5.2, C6.2, C7.2, C8.2, C9.2, C10.2, C11.2, C12.2, C13.2, C14.2, C15.2, C16.2, C24.2, C25.2, C26.2, C27.2, C28.2, C32.2, C33.2, C34.2, C35.2, C36.2, C37.2, C38.2, C39.2, C40.2, C41.2, C42.2, C43.2, C44.2, C45.2, C46.2, C47.2, C48.2, C49.2, C50.2, C51.2, C52.2, C53.2, C54.2, J1.2, R2.2, R7.2, R12.2, R15.2, R16.2, R17.2, R18.2, R22.2, R25.2, R28.2, R30.2, U1.10, U1.19, U1.20, U1.27, U1.49, U1.74, U1.99, U2.4, U3.4, U3.7, U4.1, U4.3, U4.7, U4.EXP, U6.1, U7.1, U8.2, U9.4, U9.15, U9.19, U9.25, U9.26, U9.29, U10.1, U11.1, U14.2, U15.2, U16.3, U16.PAD, U17.3, U17.PAD, U18.2, U20.C, U21.1, U21.3, U22.1
NET_U1_14: R4.1, U1.14, U21.4
NET_U1_22: C9.1, C10.1, F1.1, U1.21, U1.22
NET_U1_92: R5.1, U1.92, U3.6
NET_U1_93: R6.1, U1.93, U3.5
NET_U1_94: R7.1, U1.94
NET_U1_98: U19.3, U19.4
NET_U2_3: R8.1, U2.3
NET_U2_7: R10.1, U2.7
NET_U3_1: R11.1, U3.1
NET_U3_2: R12.1, U3.2
NET_U3_3: R13.1, U3.3
NET_U4_10: C27.1, U4.10
NET_U4_29: R14.1, U4.29
NET_U4_31: R15.1, U4.31
NET_U5_1: U4.4, U5.1
NET_U5_2: U4.2, U5.2
NET_U5_5: U4.6, U5.5
NET_U6_2: C18.1, U6.2
NET_U6_5: C17.1, U6.5
NET_U7_2: C20.1, C21.1, U7.2
NET_U7_5: C19.1, U7.5
NET_U7_13: C20.2, C21.2
NET_U8_1: C22.1, C23.1, C28.1, U4.16, U8.1
NET_U8_15: C22.2, C23.2
NET_U9_20: C37.1, C42.1, U9.20
NET_U10_2: C30.1, R17.1, U10.2
NET_U10_5: C29.1, R16.1, U10.5
NET_U11_5: C31.1, C32.1, R18.1, R19.1, U11.5
NET_U16_1: C45.1, U16.1
NET_U16_6: R21.2, R22.1, U16.6
NET_U16_8: R20.1, U16.8
NET_U17_1: C48.1, U17.1
NET_U17_6: R24.2, R25.1, U17.6
NET_U17_8: R23.1, U17.8
NET_U18_1: R27.1, R28.1, U18.1
NET_U18_3: R29.2, R30.1, U18.3
NET_U18_4: R26.1, U18.4, U21.2
NET_U19_1: R2.1, U19.1, U19.2
PROC_ADC1_IN1: U1.24, U22.3
PROC_ADC1_IN2: U1.25, U22.2
PROC_I2S2_CK: U1.52, U9.7
PROC_I2S2_SD: U1.54, U9.8
PROC_I2S2_WS: U1.51, U9.9, U9.11
PROC_I2S3_CK: U1.78, U4.24
PROC_I2S3_SD: U1.80, U4.26
PROC_I2S3_WS: U1.77, U4.23
PROC_SPI1_MISO: U1.31, U2.2
PROC_SPI1_MOSI: U1.32, U2.5
PROC_SPI1_NSS: R9.1, U1.29, U2.1
PROC_SPI1_SCK: U1.30, U2.6
VCC_S1_9V6: C46.1, C49.1, C52.1, C53.1, J1.1, R20.2, R23.2, U16.4, U17.4
VCC_TIER1_1V2: C24.1, C47.1, R21.1, U4.30, U16.5
VCC_TIER1_3V3: C1.1, C2.1, C3.1, C4.1, C5.1, C6.1, C7.1, C8.1, C15.1, C16.1, C25.1, C26.1, C33.1, C34.1, C35.1, C36.1, C38.1, C39.1, C40.1, C41.1, C43.1, C44.1, C50.1, C51.1, C54.1, F1.2, R4.2, R5.2, R6.2, R8.2, R9.2, R10.2, R11.2, R13.2, R14.2, R24.1, R26.2, R27.2, R29.1, U1.6, U1.11, U1.28, U1.50, U1.75, U1.100, U2.8, U3.8, U4.5, U4.20, U9.3, U9.5, U9.12, U9.18, U14.4, U15.4, U17.5, U18.6, U21.5
